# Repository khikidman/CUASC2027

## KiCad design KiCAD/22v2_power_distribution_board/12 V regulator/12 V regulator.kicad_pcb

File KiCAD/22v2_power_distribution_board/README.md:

1. 22V Regulator: powers motors-assigned to
2. 12V Regulator: powers jetson-assigned to
3. 5V Regulator: powers peripherals-assigned to
4. 3.3V Regulator? might not be necessary

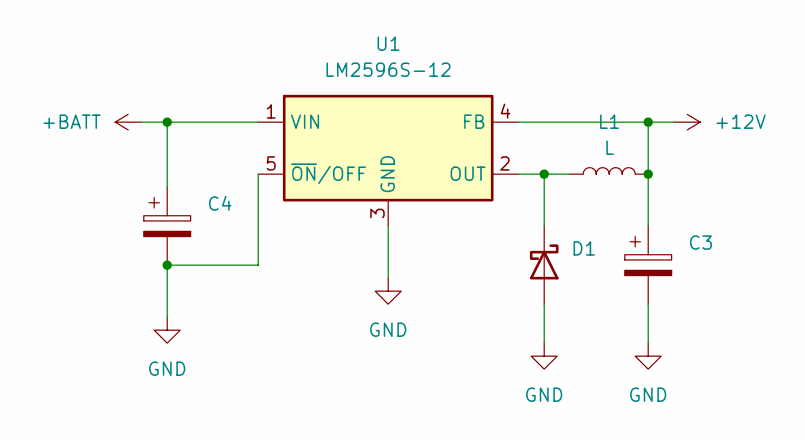
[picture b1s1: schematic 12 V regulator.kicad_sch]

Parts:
C3: C_Polarized; CP_Elec_8x10.5
C4: C_Polarized; CP_Elec_10x10.5
D1: D_Schottky; D_SMC
L1: L; L_12x12mm_H8mm
U1: LM2596S-12; TO-263-5_TabPin3

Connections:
+12V: C3.1, L1.2, U1.4 (FB)
+BATT: C4.1, U1.1 (VIN)
GND: C3.2, C4.2, D1.2 (A), U1.3 (GND), U1.5 (~ON/OFF)
unnamed: D1.1 (K), L1.1, U1.2 (OUT)

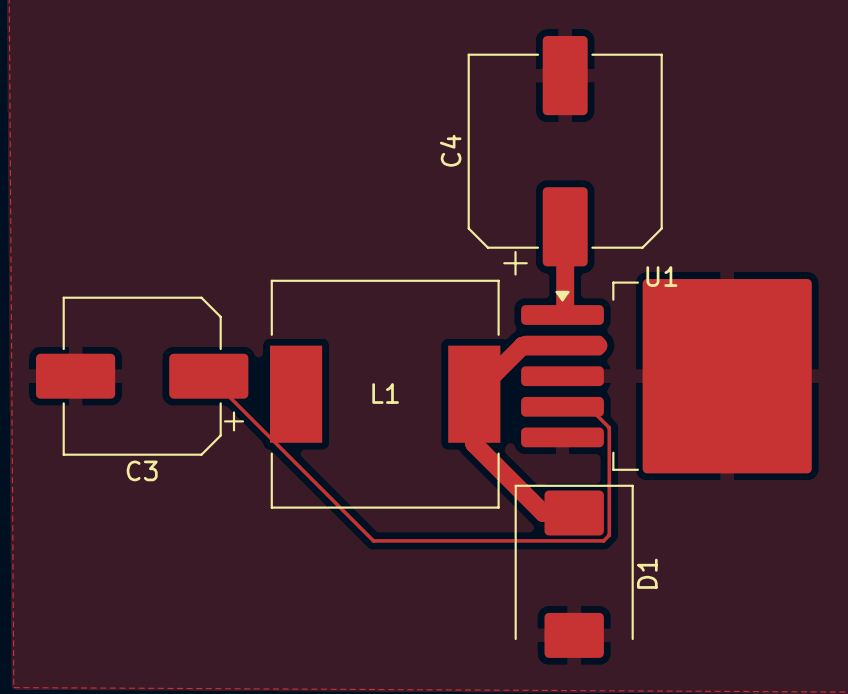
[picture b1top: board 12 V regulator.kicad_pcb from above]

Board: 2 copper layers, 5 parts (0 on the bottom side), 4 nets.
